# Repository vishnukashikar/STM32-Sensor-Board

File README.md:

# STM32 Sensor Board

A small custom board built around an **STM32C031C6** microcontroller and an **MPU-6050** 6-axis accelerometer/gyroscope (I2C), designed in KiCad.

**Status:** v1 (2026-09-17), design complete, not yet fabricated or tested.

This is a hardware design project: the repository contains the KiCad schematic and PCB layout only, with no firmware.

| Front | Back |
|---|---|
|  |  |

## Hardware overview

| Ref | Part | Role |
|---|---|---|
| U2 | STM32C031C6Tx (LQFP-48) | Main MCU |
| U3 | MPU-6050 (QFN-24, 4x4 mm) | Accelerometer + gyroscope |
| U1 | AMS1117-3.3 (SOT-223) | 5 V to 3.3 V regulator |
| J1 | USB-C receptacle | 5 V power input (VBUS) |
| Y1 | 16 MHz crystal (3225) with 16 pF load caps (C3, C5) | MCU clock |
| SW1 | SPDT slide switch | BOOT0 select (silkscreen: BOOT 0/1) |
| J4 | 1x4 header | SWD: 3V3, DIO, CLK, GND |
| J2, J3, J5 | 1x7, 1x11, 1x18 headers | GPIO breakout |
| D1 + R3 | LED + 300 ohm | Status LED |
| R4, R6 | 4.7 k | I2C pull-ups |
| FB1 + C6 | 120 ohm ferrite bead + 4.5 uF | Analog supply filtering (+3.3VA) |

Board: 2-layer, about 65.5 x 54 mm, four M2 mounting holes.

## Key connections

| Signal | U2 (MCU) pin | Goes to |
|---|---|---|
| I2C1_SCL | 29 | MPU-6050 SCL (U3 pin 23) |
| I2C1_SDA | 32 | MPU-6050 SDA (U3 pin 24) |
| MPU_INT | 33 | MPU-6050 INT (U3 pin 12) |
| SWCLK / SWDIO | 36 / 35 | J4 |
| NRST | 10 | Reset net |

The remaining MCU pins are broken out to J2, J3 and J5. See the schematic for the full pin mapping.

## Repository layout

```
hardware/   KiCad project (schematic, PCB, project file)
images/     3D renders of the board
```

## Programming and debug interface

The board exposes SWD on header J4 (3V3, DIO, CLK, GND). The USB-C port is used for power only; its data lines are not routed to the MCU.

## Opening the design

Open `hardware/stm32_sensor_board.kicad_pro` in KiCad.

## License

MIT, see [LICENSE](LICENSE).

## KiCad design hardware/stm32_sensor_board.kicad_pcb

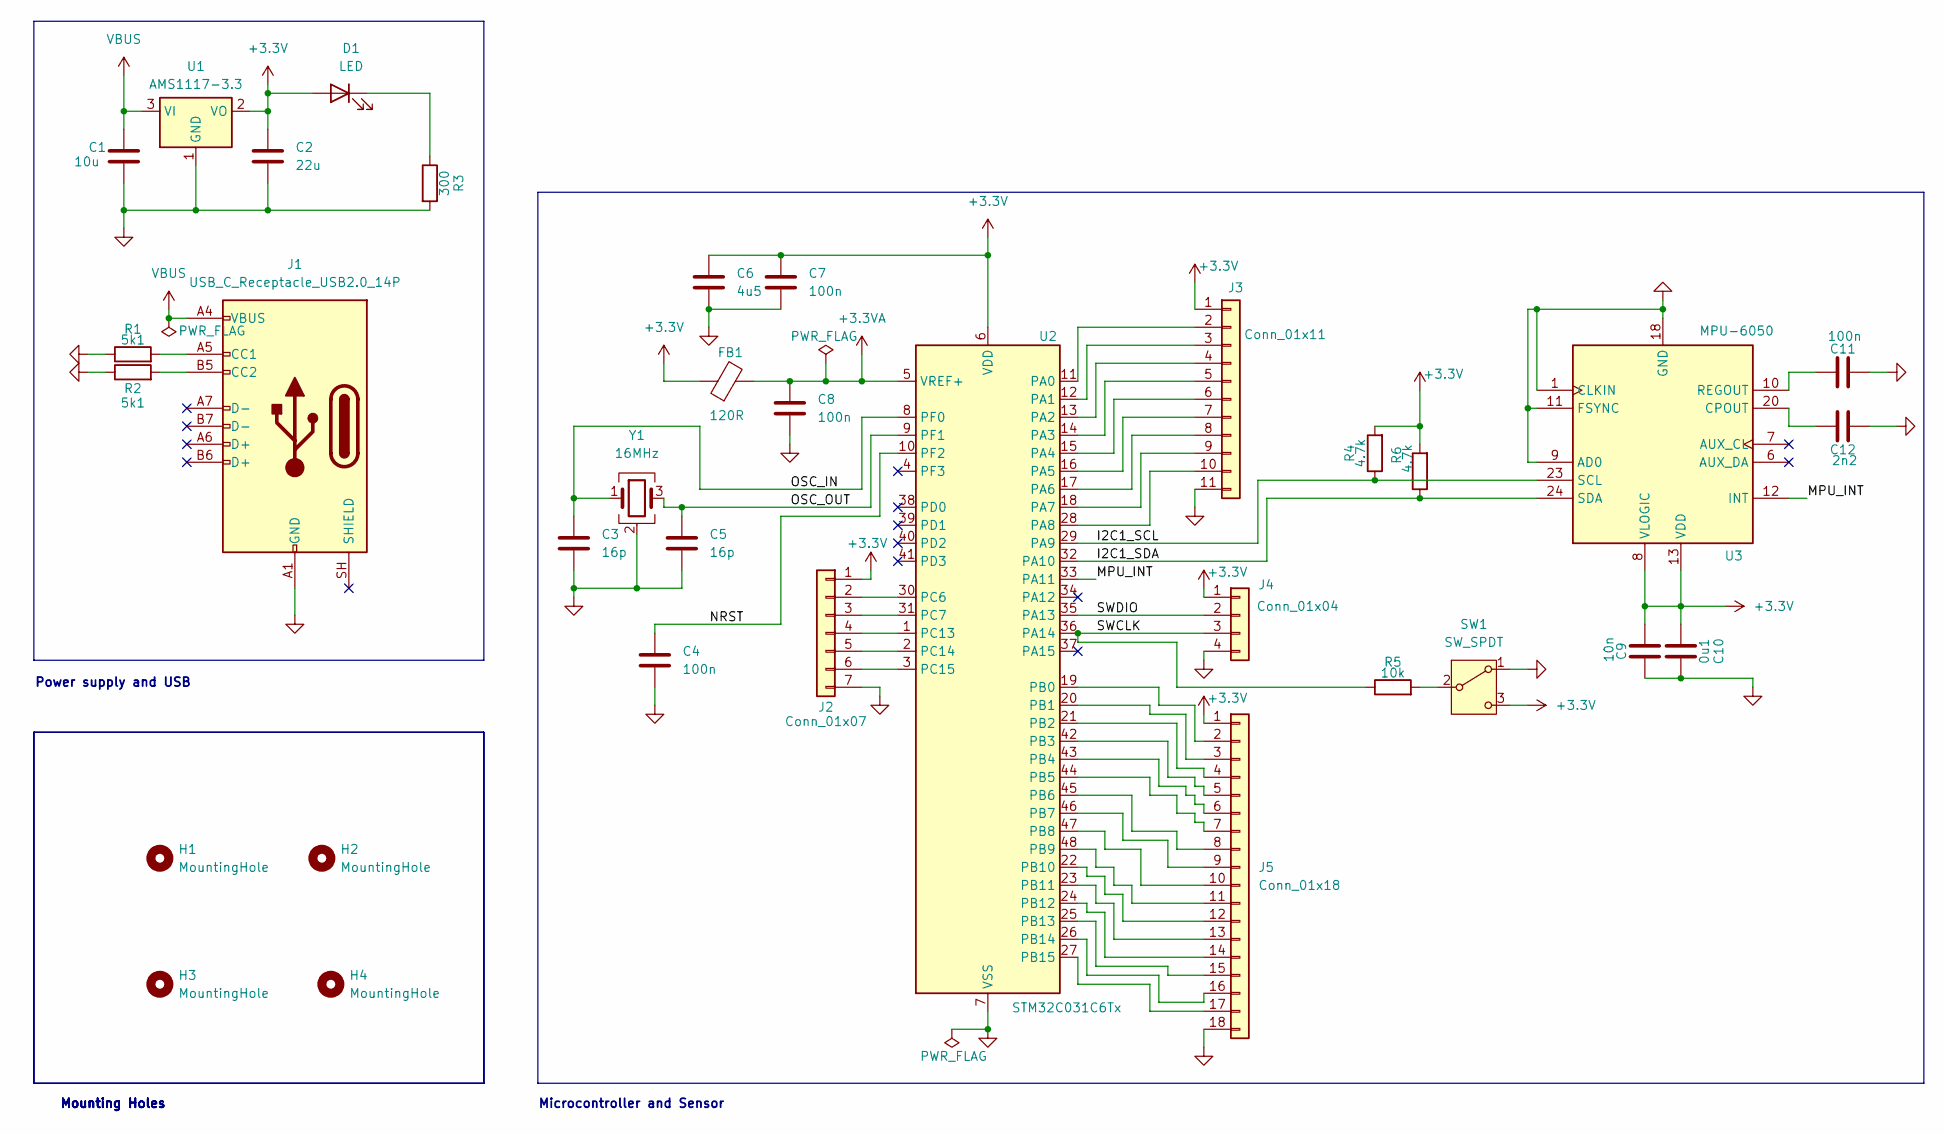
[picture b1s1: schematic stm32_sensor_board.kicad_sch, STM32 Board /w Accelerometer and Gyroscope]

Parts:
C1: 10u; C_0805_2012Metric
C2: 22u; C_1206_3216Metric
C3, C5: 16p; C_0603_1608Metric
C4, C7, C8, C11: 100n; C_0603_1608Metric
C6: 4u5; C_0805_2012Metric
C9: 10n; C_0603_1608Metric
C10: 0u1; C_0603_1608Metric
C12: 2n2; C_0603_1608Metric
D1: LED; LED_0603_1608Metric
FB1: 120R; L_0805_2012Metric
H1, H2, H3, H4: MountingHole; MountingHole_2.2mm_M2
J1: USB_C_Receptacle_USB2.0_14P; USB_C_Receptacle_GCT_USB4105-xx-A_16P_TopMnt_Horizontal
J2: Conn_01x07; PinHeader_1x07_P2.54mm_Vertical
J3: Conn_01x11; PinHeader_1x11_P2.54mm_Vertical
J4: Conn_01x04; PinHeader_1x04_P2.54mm_Vertical
J5: Conn_01x18; PinHeader_1x18_P2.54mm_Vertical
R1, R2: 5k1; R_0603_1608Metric
R3: 300; R_0603_1608Metric
R4, R6: 4.7k; R_0402_1005Metric
R5: 10k; R_0603_1608Metric
SW1: SW_SPDT; SW_Slide_SPDT_Straight_CK_OS102011MS2Q
U1: AMS1117-3.3; SOT-223-3_TabPin2
U2: STM32C031C6Tx; LQFP-48_7x7mm_P0.5mm
U3: MPU-6050; InvenSense_QFN-24_4x4mm_P0.5mm
Y1: 16MHz; Crystal_SMD_3225-4Pin_3.2x2.5mm

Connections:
+3.3V: C2.1, C6.1, C7.1, C9.2, C10.2, D1.2 (A), FB1.1, J2.1, J3.1, J4.1, J5.1, R4.2, R6.2, SW1.3 (C), U1.2 (VO), U2.6 (VDD), U3.8 (VLOGIC), U3.13 (VDD)
+3.3VA: C8.1, FB1.2, U2.5 (VREF+)
/I2C1_SCL: R4.1, U2.29 (PA9), U3.23 (SCL)
/I2C1_SDA: R6.1, U2.32 (PA10), U3.24 (SDA)
/MPU_INT: U2.33 (PA11), U3.12 (INT)
/NRST: C4.1, U2.10 (PF2)
/OSC_IN: C3.1, U2.8 (PF0), Y1.1
/OSC_OUT: C5.1, U2.9 (PF1), Y1.3
/SWCLK: J4.3, R5.1, U2.36 (PA14)
/SWDIO: J4.2, U2.35 (PA13)
GND: C1.2, C2.2, C3.2, C4.2, C5.2, C6.2, C7.2, C8.2, C9.1, C10.1, C11.2, C12.2, J1.A1 (GND), J1.A12 (GND), J1.B1 (GND), J1.B12 (GND), J1.SH (SHIELD), J2.7, J3.11, J4.4, J5.18, R1.1, R2.1, R3.2, SW1.1 (A), U1.1 (GND), U2.7 (VSS), U3.1 (CLKIN), U3.9 (AD0), U3.11 (FSYNC), U3.18 (GND), Y1.2 (G), Y1.4 (G)
unnamed: D1.1 (K), R3.1
unnamed: J1.A5 (CC1), R1.2
unnamed: J1.B5 (CC2), R2.2
unnamed: J2.2, U2.30 (PC6)
unnamed: J2.3, U2.31 (PC7)
unnamed: J2.4, U2.1 (PC13)
unnamed: J2.5, U2.2 (PC14)
unnamed: J2.6, U2.3 (PC15)
unnamed: J3.2, U2.11 (PA0)
unnamed: J3.3, U2.12 (PA1)
unnamed: J3.4, U2.13 (PA2)
unnamed: J3.5, U2.14 (PA3)
unnamed: J3.6, U2.15 (PA4)
unnamed: J3.7, U2.16 (PA5)
unnamed: J3.8, U2.17 (PA6)
unnamed: J3.9, U2.18 (PA7)
unnamed: J3.10, U2.28 (PA8)
unnamed: J5.2, U2.19 (PB0)
unnamed: J5.3, U2.20 (PB1)
unnamed: J5.4, U2.21 (PB2)
unnamed: J5.5, U2.42 (PB3)
unnamed: J5.6, U2.43 (PB4)
unnamed: J5.7, U2.44 (PB5)
unnamed: J5.8, U2.45 (PB6)
unnamed: J5.9, U2.46 (PB7)
unnamed: J5.10, U2.47 (PB8)
unnamed: J5.11, U2.48 (PB9)
unnamed: J5.12, U2.22 (PB10)
unnamed: J5.13, U2.23 (PB11)
unnamed: J5.14, U2.24 (PB12)
unnamed: J5.15, U2.25 (PB13)
unnamed: J5.16, U2.26 (PB14)
unnamed: J5.17, U2.27 (PB15)
unnamed: R5.2, SW1.2 (B)
unnamed: C12.1, U3.20 (CPOUT)
unnamed: C11.1, U3.10 (REGOUT)
VBUS: C1.1, J1.A4 (VBUS), J1.A9 (VBUS), J1.B4 (VBUS), J1.B9 (VBUS), U1.3 (VI)

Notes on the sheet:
Mounting Holes
Power supply and USB
Microcontroller and Sensor

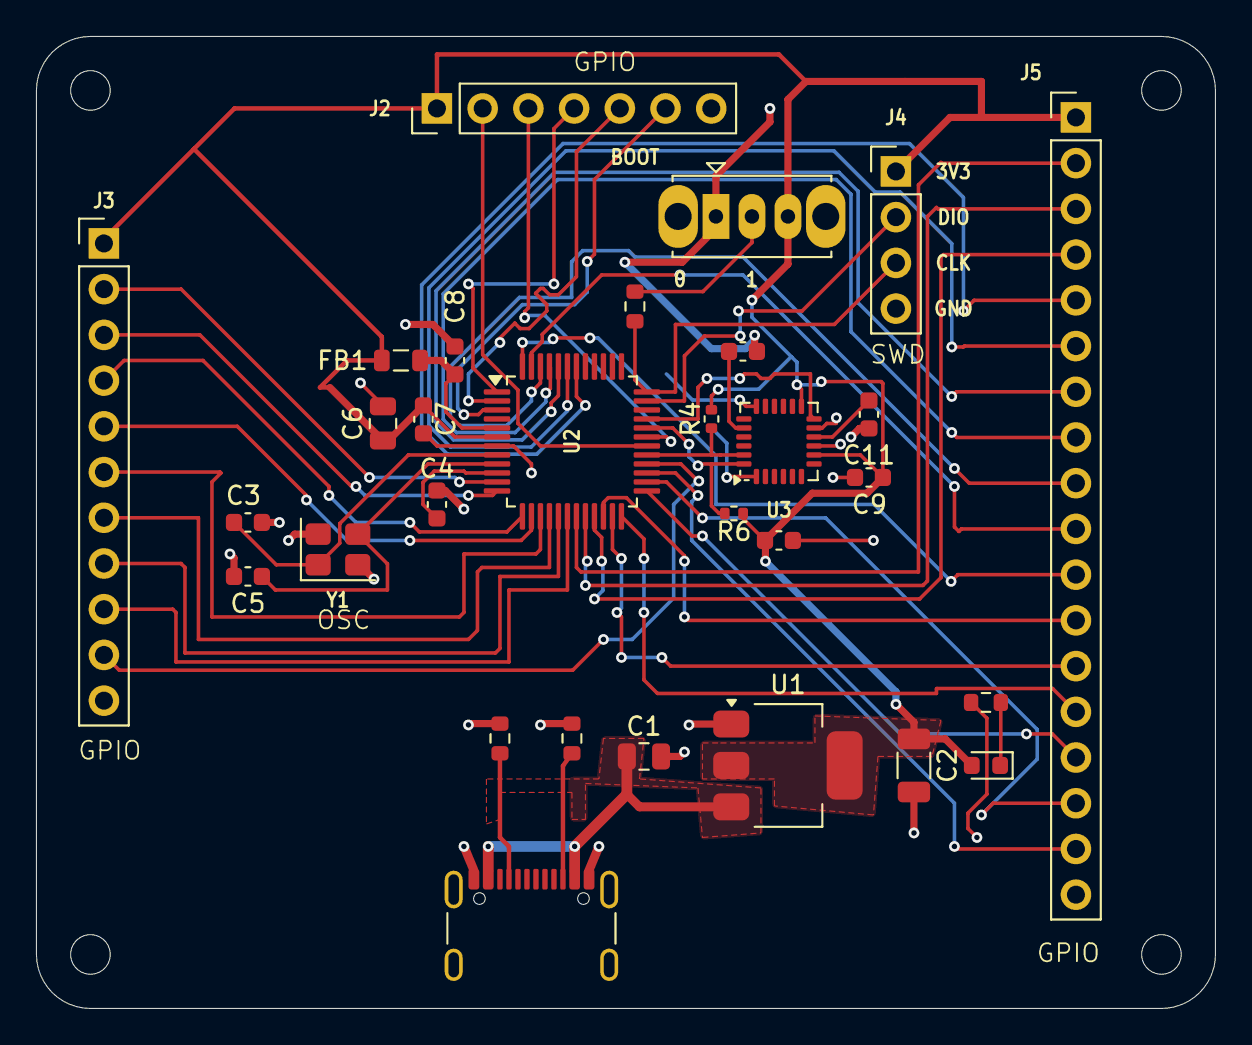
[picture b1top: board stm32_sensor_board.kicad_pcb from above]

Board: 2 copper layers, 65.5 x 54.0 mm, 34 parts (0 on the bottom side), 48 nets.
